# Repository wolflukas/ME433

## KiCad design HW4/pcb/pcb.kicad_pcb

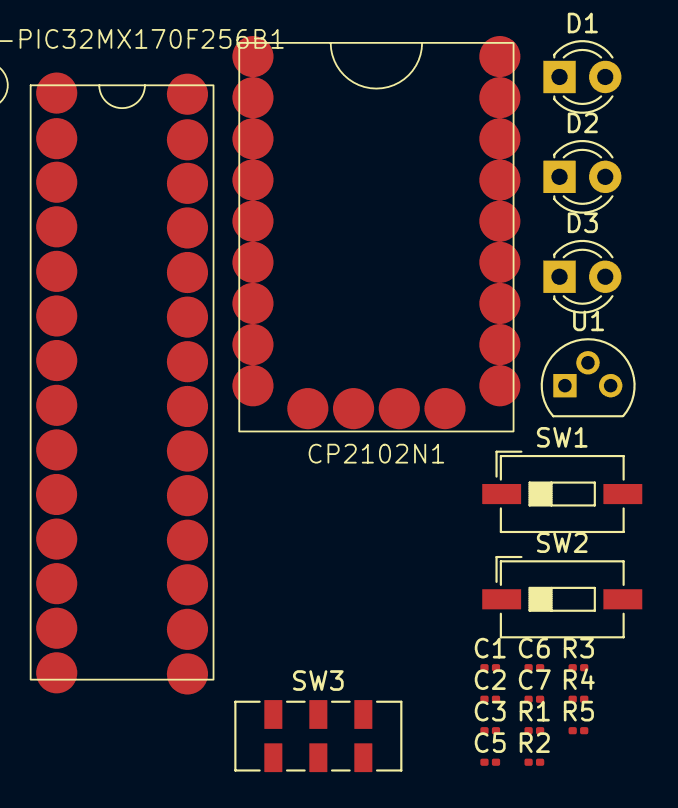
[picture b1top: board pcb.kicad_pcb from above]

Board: 2 copper layers, 21 parts (0 on the bottom side), 14 nets, no tracks yet.

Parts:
BATTERY1: Battery_CR1225
C1: 0.1 uF; C_0201_0603Metric
C2: 0.1uF; C_0201_0603Metric
C3, C5, C6, C7: 1uF; C_0201_0603Metric
CP2102N1: c2102n
D1, D2, D3: LED; LED_D3.0mm
R1, R2: 10k; R_0201_0603Metric
R3, R4, R5: 330; R_0201_0603Metric
SW1: MCLR; SW_DIP_SPSTx01_Slide_6.7x4.1mm_W6.73mm_P2.54mm_LowProfile_J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
SW2: USER; SW_DIP_SPSTx01_Slide_6.7x4.1mm_W6.73mm_P2.54mm_LowProfile_J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
SW3: SW_DPDT_x2; SW_DPDT_CK_JS202011JCQN
U1: AP7384-33V; TO-92L
U1-PIC32MX170F256B1: PIC322MX170F256B

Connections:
+3.3V: C2.1, C3.1, C5.1, C6.1, D1.2 (A), D2.2 (A), D3.2 (A), R1.1, R2.1, U1.1 (VO), U1-PIC32MX170F256B1.20 (Vcap), U1-PIC32MX170F256B1.28 (AVdd)
+5V: CP2102N1.4, SW3.3 (C)
/GREEN: R3.2, U1-PIC32MX170F256B1.11 (B4)
/MCLR: R1.2, SW1.2, U1-PIC32MX170F256B1.1 (MCLR)
/U1RX: CP2102N1.3, U1-PIC32MX170F256B1.9 (A2)
/U1TX: CP2102N1.2, U1-PIC32MX170F256B1.7 (B3)
/USER: R2.2, SW2.2, U1-PIC32MX170F256B1.12 (A4)
/YELLOW: R4.2, U1-PIC32MX170F256B1.14 (B5)
GND: C1.2, C2.2, C3.2, C5.2, C6.2, C7.2, CP2102N1.6, R5.2, SW1.1, SW2.1, U1-PIC32MX170F256B1.8 (Vss), U1-PIC32MX170F256B1.19 (Vss), U1-PIC32MX170F256B1.27 (AVss)
unnamed: D1.1 (K), R3.1
unnamed: D2.1 (K), R4.1
unnamed: D3.1 (K), R5.1
unnamed: C7.1, SW3.2 (B), U1.3 (VI)
unnamed: C1.1, U1-PIC32MX170F256B1.13 (Vdd)

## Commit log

2023-05-19 .gitignore
2023-05-30 Homework 4
2023-05-30 Homework 4 Images
2023-05-30 Create Homework 4 Images
2023-05-30 Update Homework 4 Images
2023-05-31 Homework 4 Finishing
2023-05-31 HW9 files
2023-05-31 Homework 9
2023-06-07 Homework 3
2023-06-08 HW12
2023-06-09 HW10(incomplete)
